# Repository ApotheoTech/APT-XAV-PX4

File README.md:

# APT-XAV-PX4
Copyright 2022 ApotheoTech LLC

# Description

APT-XAV-PX4 is a PX4 based flight controller following FMUv5X. It has a SODIMM connector that is compatible with Nvidia's Jetson Nano, Xavier NX, and TX2 boards. It is a derivative of AntMicros' Jetson Nano Baseboard. I converted the board to Kicad using an Altium to Kicad converter available in the nightly builds of Kicad 6.0.

The APT-XAV-PX4 breaks out Ethernet, USB-C, HDMI, DisplayPort, 2 Raspberry PiCam MIPI connectors (2lane and 4 lane) and a connector for Alvium Sensors. The pinout for the Alvium connector must be used in conjunction with AntMicro's flex cables.

https://user-images.githubusercontent.com/43386283/153778050-1cda64f4-45f2-4941-b6fc-7a415ffa1639.mp4

# Where to Buy

The prototypes for this board were not built due to a combination of a lack of funds, and a redirection of focus to another project February of 2021. If you are interested in supporting the project, or wish to create the prototypes, I have most of the BOM in stock. 

For inquires email me at chance189[at]knights.ucf.edu

# Referenced Works
* [AntMicro Jetson Nano BaseBoard](https://github.com/antmicro/jetson-nano-baseboard)
* [PX4 Hardware](https://github.com/pixhawk/Hardware)

# Licensing

I was unsure how to license it based on AntMicro's Apache License. Due to recreating the work from Altium to Kicad, I was unable to preserve the "unmodified" files from the modified files. All modified files are released under the GPLV3 License.

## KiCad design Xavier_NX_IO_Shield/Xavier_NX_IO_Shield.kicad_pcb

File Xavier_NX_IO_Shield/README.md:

# APT-XAV-PX4 IO SHIELD
Copyright 2022 ApotheoTech LLC

# Description

The IO shield breaks out all the signals to usable interfacing connectors as specified in DS-010 (Pixhawk Autopilot Bus Standard) Revision 0.4.0. 
Interface includes 8 PWM FMU channels, 8 IO PWM channels, SBUS, GPS, UART, SPI, and CANBUS. 

# Where to Buy

The prototypes for this board were not built due to a combination of a lack of funds, and a redirection of focus to another project February of 2021. If you are interested in supporting the project, or wish to create the prototypes, I have most of the BOM in stock. 

For inquires email me at chance189[at]knights.ucf.edu

# Referenced Works
* [PX4 Hardware](https://github.com/pixhawk/Hardware)

# Licensing

Released under the GPLV3 License.

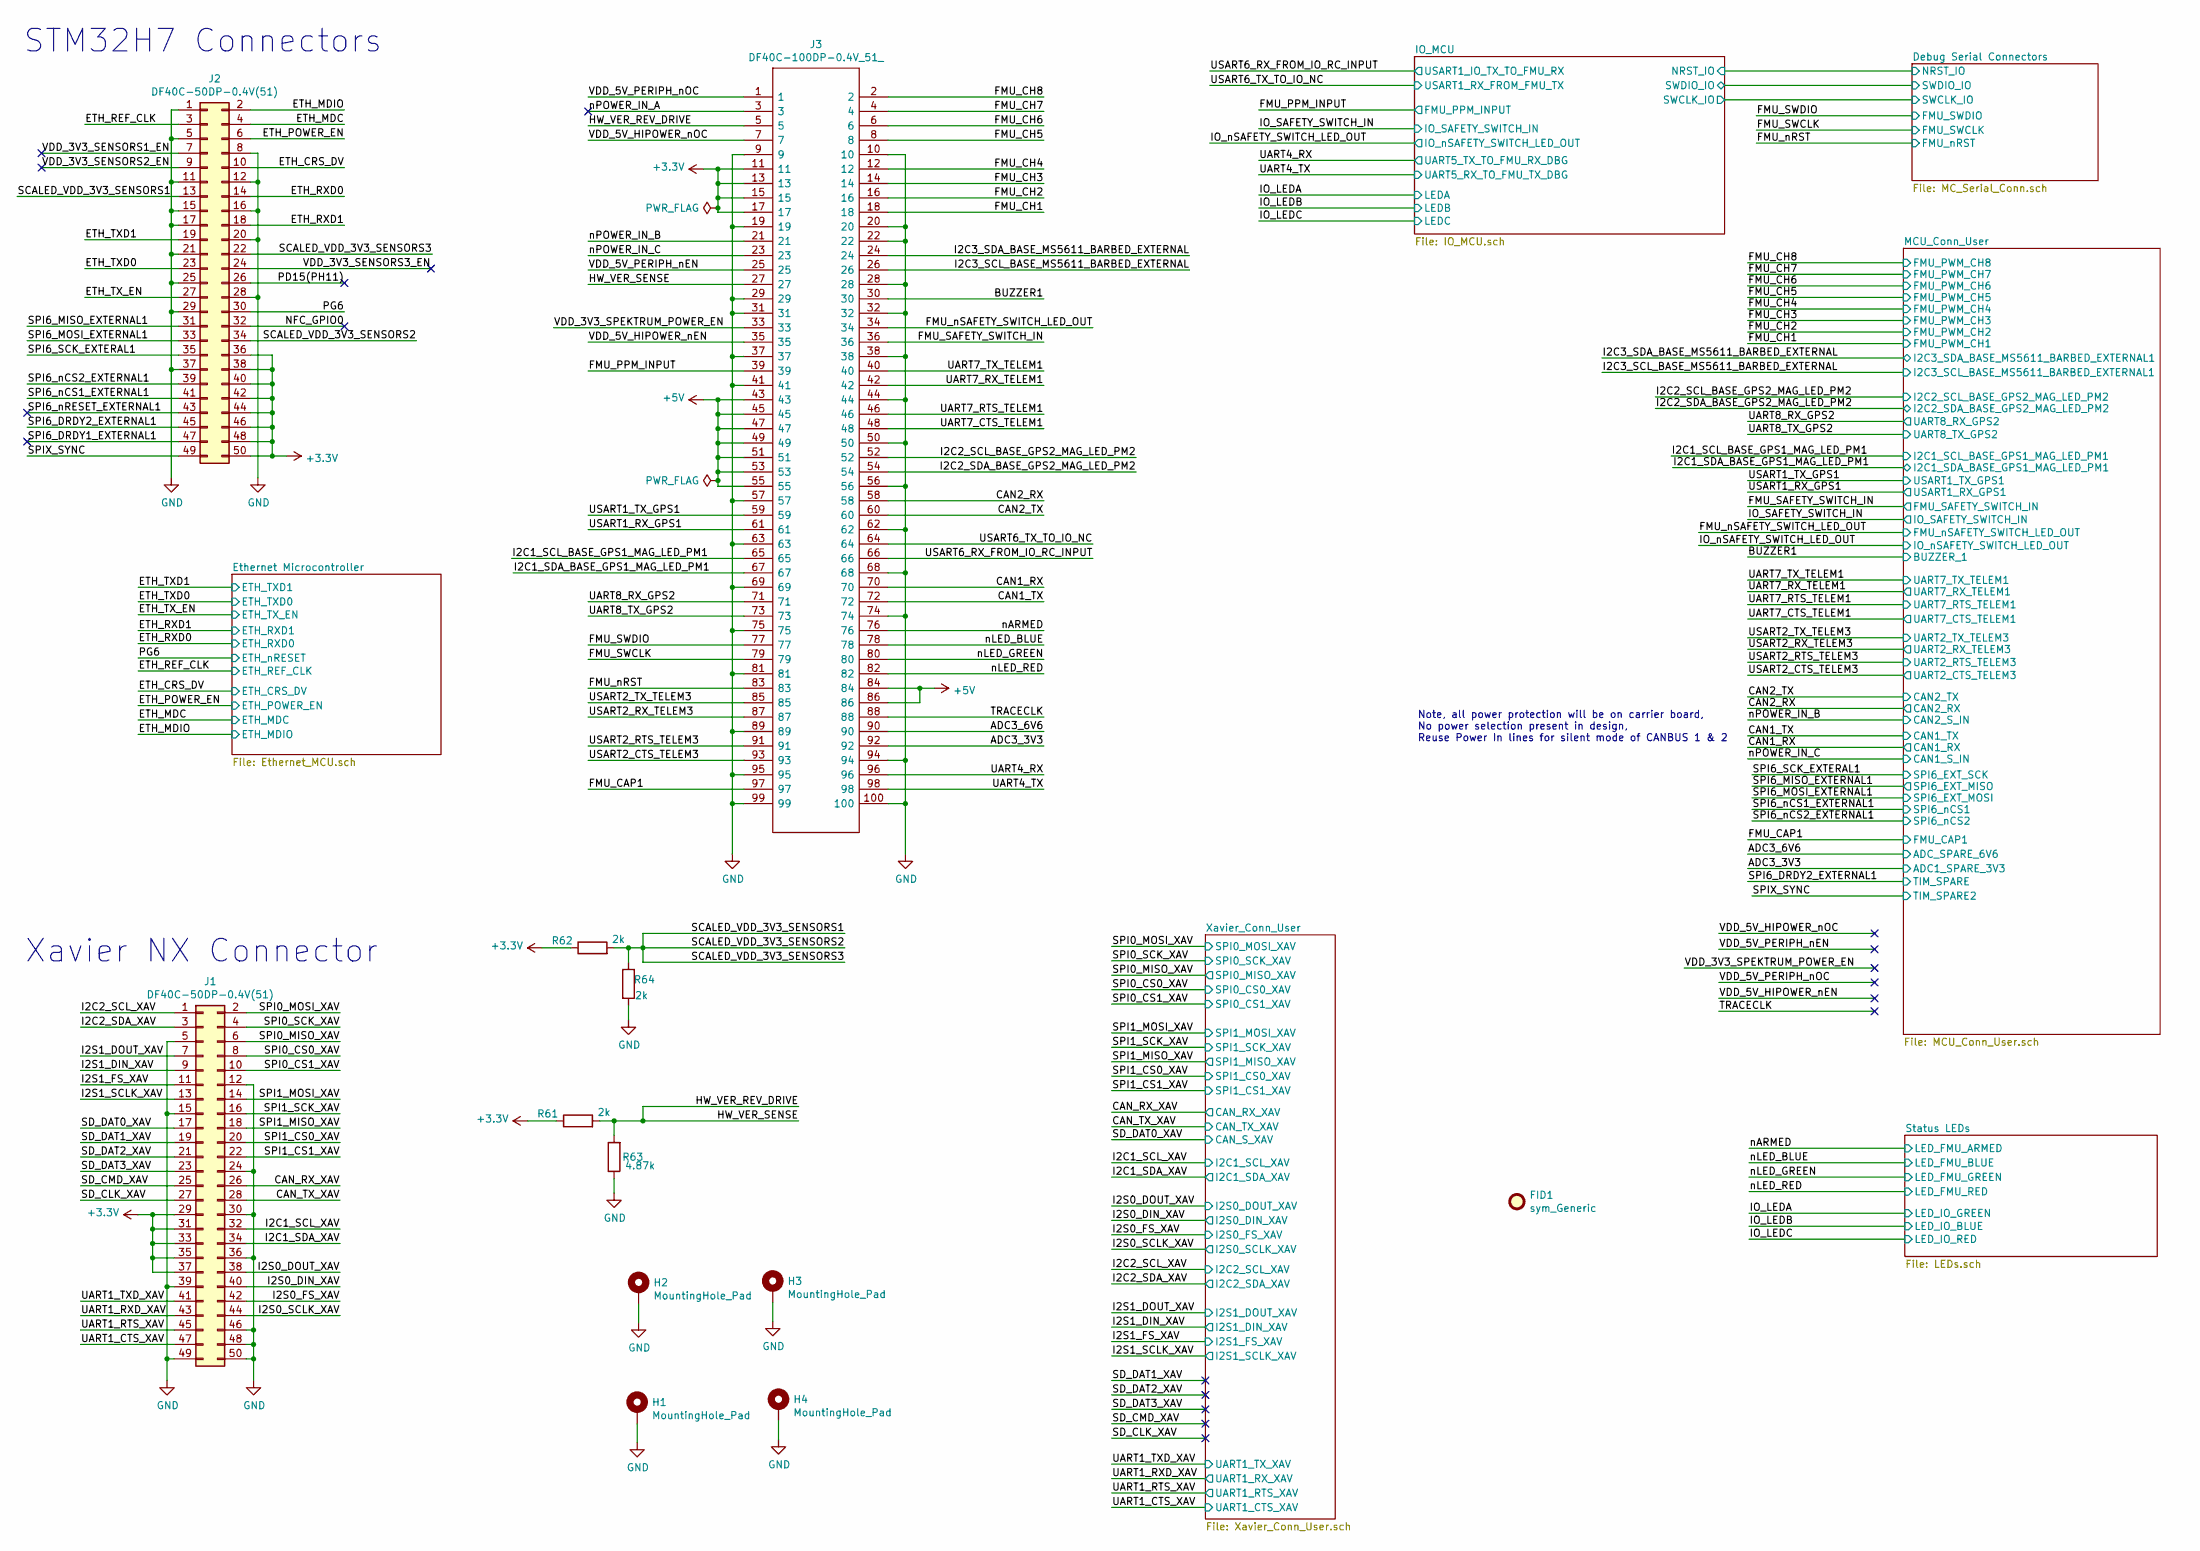
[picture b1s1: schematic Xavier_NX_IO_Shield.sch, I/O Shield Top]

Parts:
FID1: sym_Generic; ApotheoTech_Sym
H1: MountingHole_Pad; 9774015151R
H2, H3, H4: MountingHole_Pad; MountingHole_2.5mm_Pad
J1, J2: DF40C-50DP-0.4V(51); DF40C50DP04V51
J3: DF40C-100DP-0.4V_51_; DF40C100DP04V51; Mouser Part Number 798-DF40C100DP0.4V51
R61, R62, R64: 2k; R_0402_1005Metric; PartNumber CRCW04022K00FKED
R63: 4.87k; R_0402_1005Metric; PartNumber ERJ-2RKF4871X

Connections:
+3V3: J1.29, J1.31, J1.33, J1.35, J1.37, J2.36, J2.38, J2.40, J2.42, J2.44, J2.46, J2.48, J2.50, J3.11, J3.13, J3.15, J3.17, R61.1, R62.1; also elsewhere on the board
+5V: J3.43, J3.45, J3.47, J3.49, J3.51, J3.53, J3.55, J3.84, J3.86; also elsewhere on the board
/ADC3_3V3: J3.92; also elsewhere on the board
/ADC3_6V6: J3.90; also elsewhere on the board
/BUZZER1: J3.30; also elsewhere on the board
/CAN1_RX: J3.70; also elsewhere on the board
/CAN1_TX: J3.72; also elsewhere on the board
/CAN2_RX: J3.58; also elsewhere on the board
/CAN2_TX: J3.60; also elsewhere on the board
/CAN_RX_XAV: J1.26; also elsewhere on the board
/CAN_TX_XAV: J1.28; also elsewhere on the board
/ETH_CRS_DV: J2.10; also elsewhere on the board
/ETH_MDC: J2.4; also elsewhere on the board
/ETH_MDIO: J2.2; also elsewhere on the board
/ETH_POWER_EN: J2.6; also elsewhere on the board
/ETH_REF_CLK: J2.3; also elsewhere on the board
/ETH_RXD0: J2.14; also elsewhere on the board
/ETH_RXD1: J2.18; also elsewhere on the board
/ETH_TXD0: J2.23; also elsewhere on the board
/ETH_TXD1: J2.19; also elsewhere on the board
/ETH_TX_EN: J2.27; also elsewhere on the board
/FMU_CAP1: J3.97; also elsewhere on the board
/FMU_CH1: J3.18; also elsewhere on the board
/FMU_CH2: J3.16; also elsewhere on the board
/FMU_CH3: J3.14; also elsewhere on the board
/FMU_CH4: J3.12; also elsewhere on the board
/FMU_CH5: J3.8; also elsewhere on the board
/FMU_CH6: J3.6; also elsewhere on the board
/FMU_CH7: J3.4; also elsewhere on the board
/FMU_CH8: J3.2; also elsewhere on the board
/FMU_PPM_INPUT: J3.39; also elsewhere on the board
/FMU_SAFETY_SWITCH_IN: J3.36; also elsewhere on the board
/FMU_SWCLK: J3.79; also elsewhere on the board
/FMU_SWDIO: J3.77; also elsewhere on the board
/FMU_nRST: J3.83; also elsewhere on the board
/FMU_nSAFETY_SWITCH_LED_OUT: J3.34; also elsewhere on the board
/HW_VER_REV_DRIVE: J3.5, J3.27, R61.2, R63.2
/I2C1_SCL_BASE_GPS1_MAG_LED_PM1: J3.65; also elsewhere on the board
/I2C1_SCL_XAV: J1.32; also elsewhere on the board
/I2C1_SDA_BASE_GPS1_MAG_LED_PM1: J3.67; also elsewhere on the board
/I2C1_SDA_XAV: J1.34; also elsewhere on the board
/I2C2_SCL_BASE_GPS2_MAG_LED_PM2: J3.52; also elsewhere on the board
/I2C2_SCL_XAV: J1.1; also elsewhere on the board
/I2C2_SDA_BASE_GPS2_MAG_LED_PM2: J3.54; also elsewhere on the board
/I2C2_SDA_XAV: J1.3; also elsewhere on the board
/I2C3_SCL_BASE_MS5611_BARBED_EXTERNAL: J3.26; also elsewhere on the board
/I2C3_SDA_BASE_MS5611_BARBED_EXTERNAL: J3.24; also elsewhere on the board
/I2S0_DIN_XAV: J1.40; also elsewhere on the board
/I2S0_DOUT_XAV: J1.38; also elsewhere on the board
/I2S0_FS_XAV: J1.42; also elsewhere on the board
/I2S0_SCLK_XAV: J1.44; also elsewhere on the board
/I2S1_DIN_XAV: J1.9; also elsewhere on the board
/I2S1_DOUT_XAV: J1.7; also elsewhere on the board
/I2S1_FS_XAV: J1.11; also elsewhere on the board
/I2S1_SCLK_XAV: J1.13; also elsewhere on the board
/NFC_GPIO0: J2.32
/PD15(PH11): J2.26
/PG6: J2.30; also elsewhere on the board
/SCALED_VDD_3V3_SENSORS1: J2.13, J2.22, J2.34, R62.2, R64.1
/SD_CLK_XAV: J1.27
/SD_CMD_XAV: J1.25
/SD_DAT0_XAV: J1.17; also elsewhere on the board
/SD_DAT1_XAV: J1.19
/SD_DAT2_XAV: J1.21
/SD_DAT3_XAV: J1.23
/SPI0_CS0_XAV: J1.8; also elsewhere on the board
/SPI0_CS1_XAV: J1.10; also elsewhere on the board
/SPI0_MISO_XAV: J1.6; also elsewhere on the board
/SPI0_MOSI_XAV: J1.2; also elsewhere on the board
/SPI0_SCK_XAV: J1.4; also elsewhere on the board
/SPI1_CS0_XAV: J1.20; also elsewhere on the board
/SPI1_CS1_XAV: J1.22; also elsewhere on the board
/SPI1_MISO_XAV: J1.18; also elsewhere on the board
/SPI1_MOSI_XAV: J1.14; also elsewhere on the board
/SPI1_SCK_XAV: J1.16; also elsewhere on the board
/SPI6_DRDY1_EXTERNAL1: J2.47
/SPI6_DRDY2_EXTERNAL1: J2.45; also elsewhere on the board
/SPI6_MISO_EXTERNAL1: J2.31; also elsewhere on the board
/SPI6_MOSI_EXTERNAL1: J2.33; also elsewhere on the board
/SPI6_SCK_EXTERAL1: J2.35; also elsewhere on the board
/SPI6_nCS1_EXTERNAL1: J2.41; also elsewhere on the board
/SPI6_nCS2_EXTERNAL1: J2.39; also elsewhere on the board
/SPI6_nRESET_EXTERNAL1: J2.43
/SPIX_SYNC: J2.49; also elsewhere on the board
/TRACECLK: J3.88
/UART1_CTS_XAV: J1.47; also elsewhere on the board
/UART1_RTS_XAV: J1.45; also elsewhere on the board
/UART1_RXD_XAV: J1.43; also elsewhere on the board
/UART1_TXD_XAV: J1.41; also elsewhere on the board
/UART4_RX: J3.96; also elsewhere on the board
/UART4_TX: J3.98; also elsewhere on the board
/UART7_CTS_TELEM1: J3.48; also elsewhere on the board
/UART7_RTS_TELEM1: J3.46; also elsewhere on the board
/UART7_RX_TELEM1: J3.42; also elsewhere on the board
/UART7_TX_TELEM1: J3.40; also elsewhere on the board
/UART8_RX_GPS2: J3.71; also elsewhere on the board
/UART8_TX_GPS2: J3.73; also elsewhere on the board
/USART1_RX_GPS1: J3.61; also elsewhere on the board
/USART1_TX_GPS1: J3.59; also elsewhere on the board
/USART2_CTS_TELEM3: J3.93; also elsewhere on the board
/USART2_RTS_TELEM3: J3.91; also elsewhere on the board
/USART2_RX_TELEM3: J3.87; also elsewhere on the board
/USART2_TX_TELEM3: J3.85; also elsewhere on the board
/USART6_RX_FROM_IO_RC_INPUT: J3.66; also elsewhere on the board
/USART6_TX_TO_IO_NC: J3.64; also elsewhere on the board
/VDD_3V3_SENSORS1_EN: J2.7
/VDD_3V3_SENSORS2_EN: J2.9
/VDD_3V3_SENSORS3_EN: J2.24
/VDD_3V3_SPEKTRUM_POWER_EN: J3.33
/VDD_5V_HIPOWER_nEN: J3.35
/VDD_5V_HIPOWER_nOC: J3.7
/VDD_5V_PERIPH_nEN: J3.25
/VDD_5V_PERIPH_nOC: J3.1
/nARMED: J3.76; also elsewhere on the board
/nLED_BLUE: J3.78; also elsewhere on the board
/nLED_GREEN: J3.80; also elsewhere on the board
/nLED_RED: J3.82; also elsewhere on the board
/nPOWER_IN_A: J3.3
/nPOWER_IN_B: J3.21; also elsewhere on the board
/nPOWER_IN_C: J3.23; also elsewhere on the board
GND: H1.1, H2.1, H3.1, H4.1, J1.5, J1.12, J1.15, J1.24, J1.30, J1.36, J1.39, J1.46, J1.48, J1.49, J1.50, J2.1, J2.5, J2.8, J2.11, J2.12, J2.15, J2.16, J2.17, J2.20, J2.21, J2.25, J2.28, J2.29, J2.37, J3.9, J3.10, J3.19, J3.20, J3.22, J3.28, J3.29, J3.31, J3.32, J3.37, J3.38, J3.41, J3.44, J3.50, J3.56, J3.57, J3.62, J3.63, J3.68, J3.69, J3.74, J3.75, J3.81, J3.89, J3.94, J3.95, J3.99, J3.100, R63.1, R64.2; also elsewhere on the board

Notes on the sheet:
STM32H7 Connectors
Xavier NX Connector
Note, all power protection will be on carrier board, No power selection present in design, Reuse Power In lines for silent mode of CANBUS 1 & 2

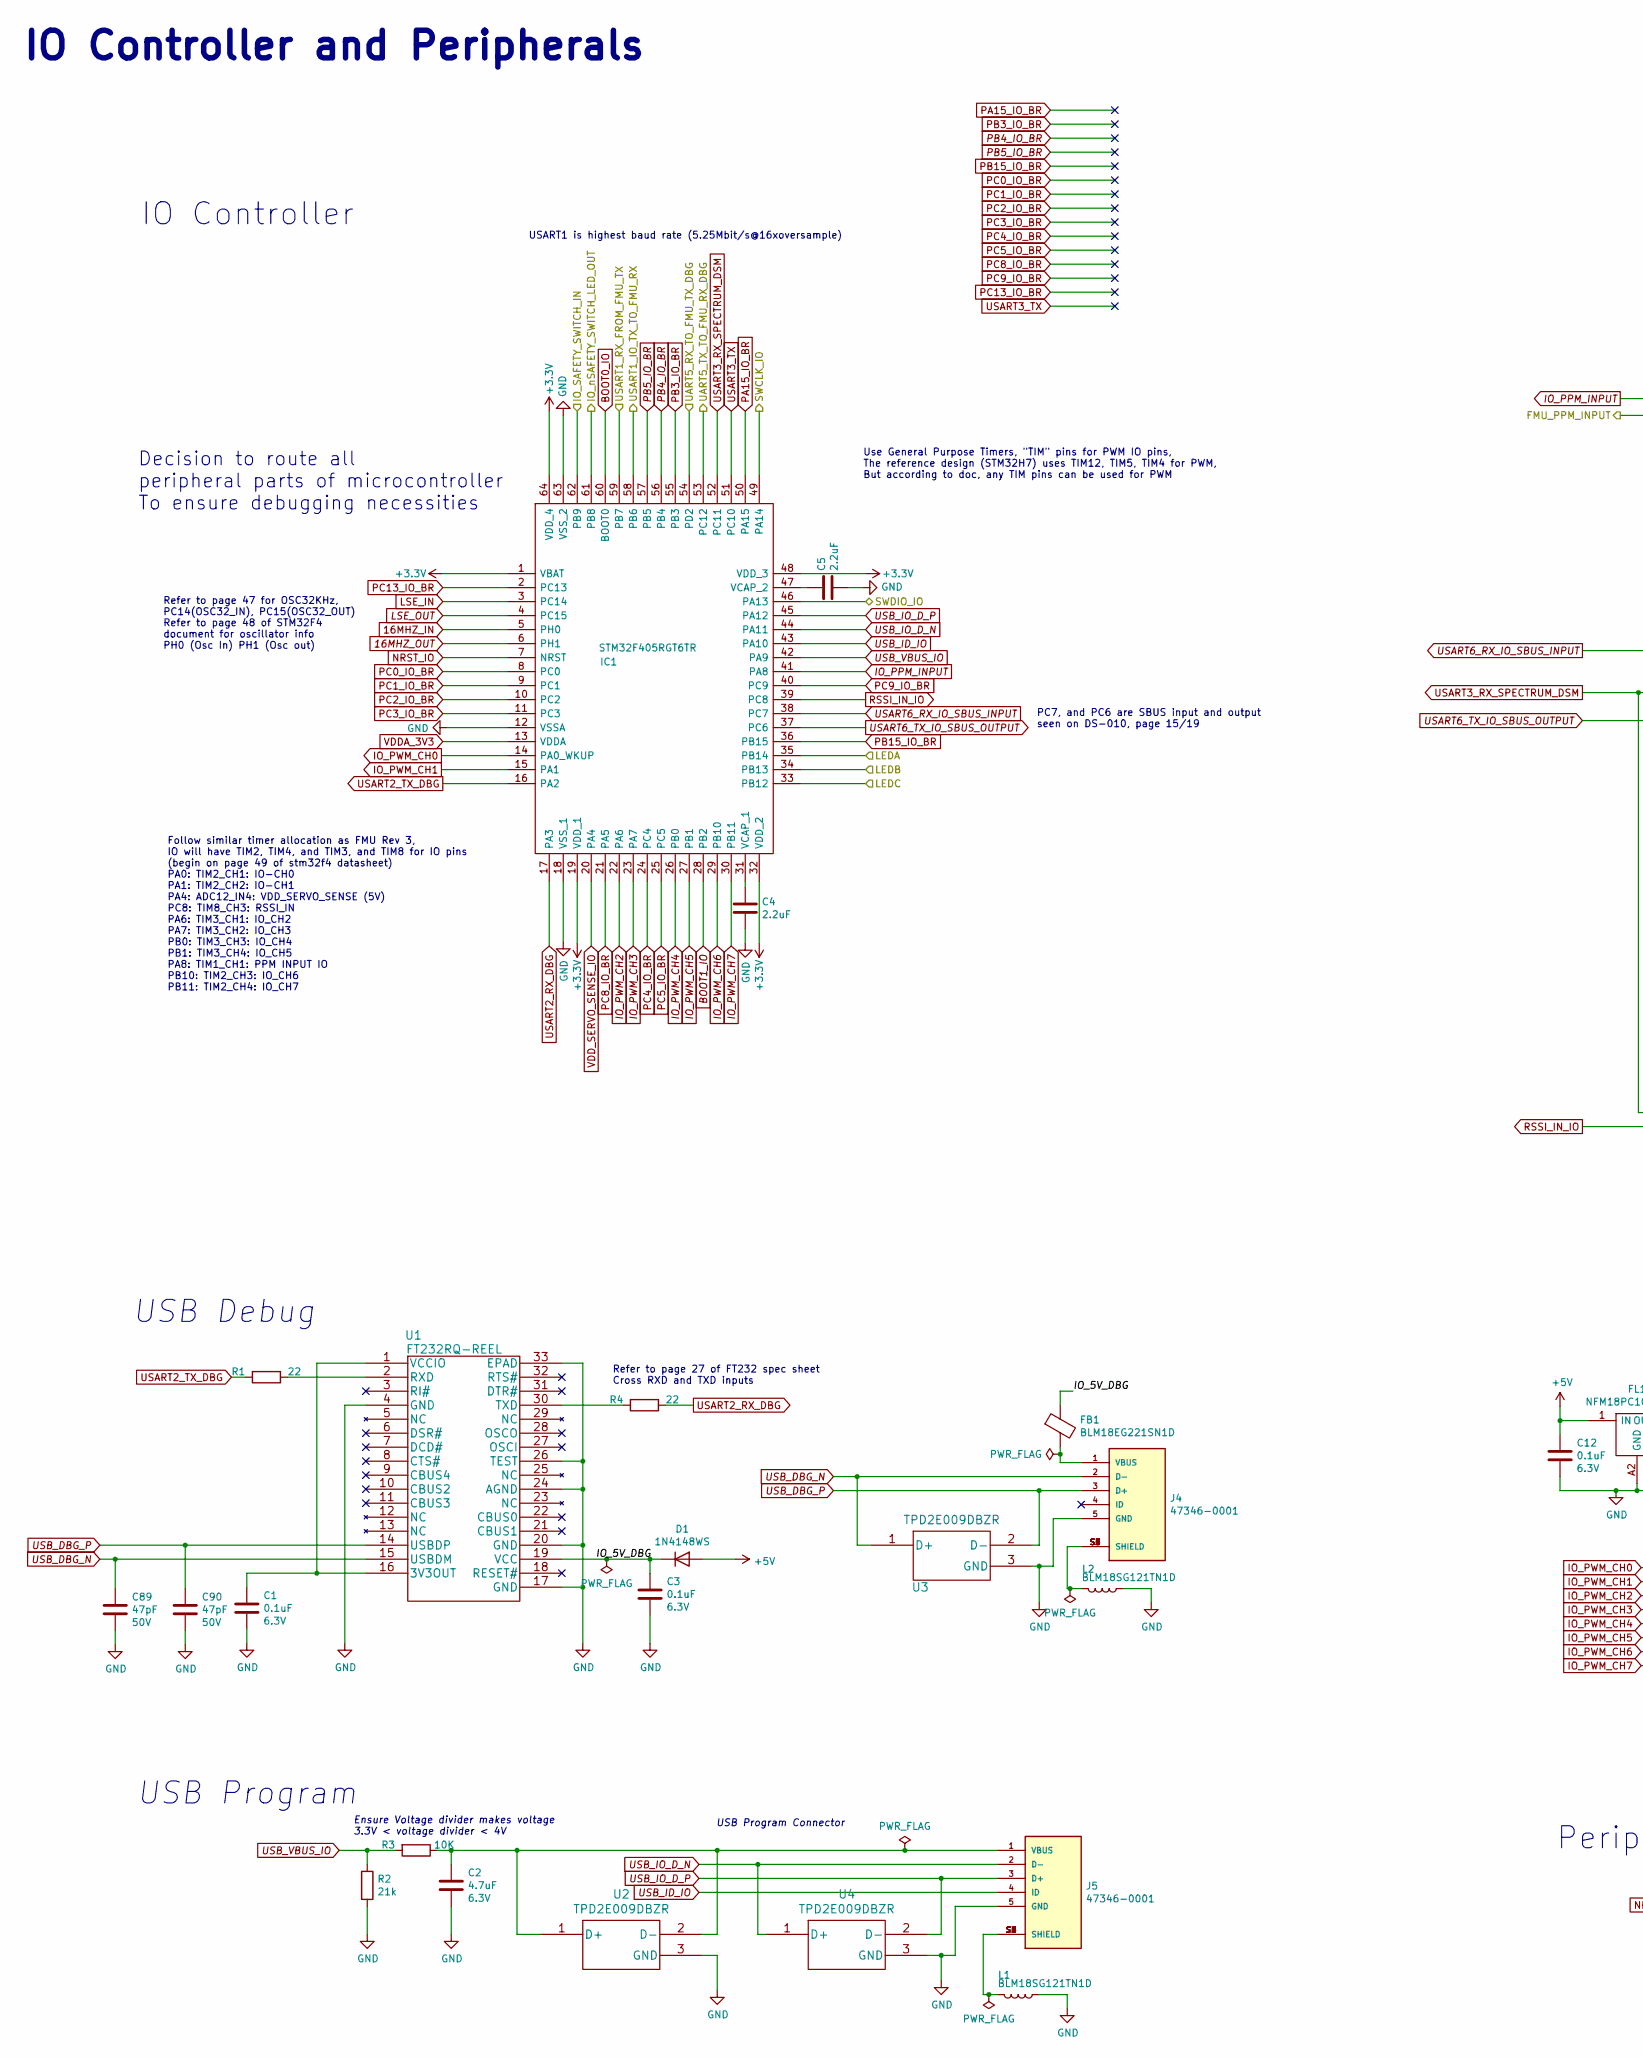
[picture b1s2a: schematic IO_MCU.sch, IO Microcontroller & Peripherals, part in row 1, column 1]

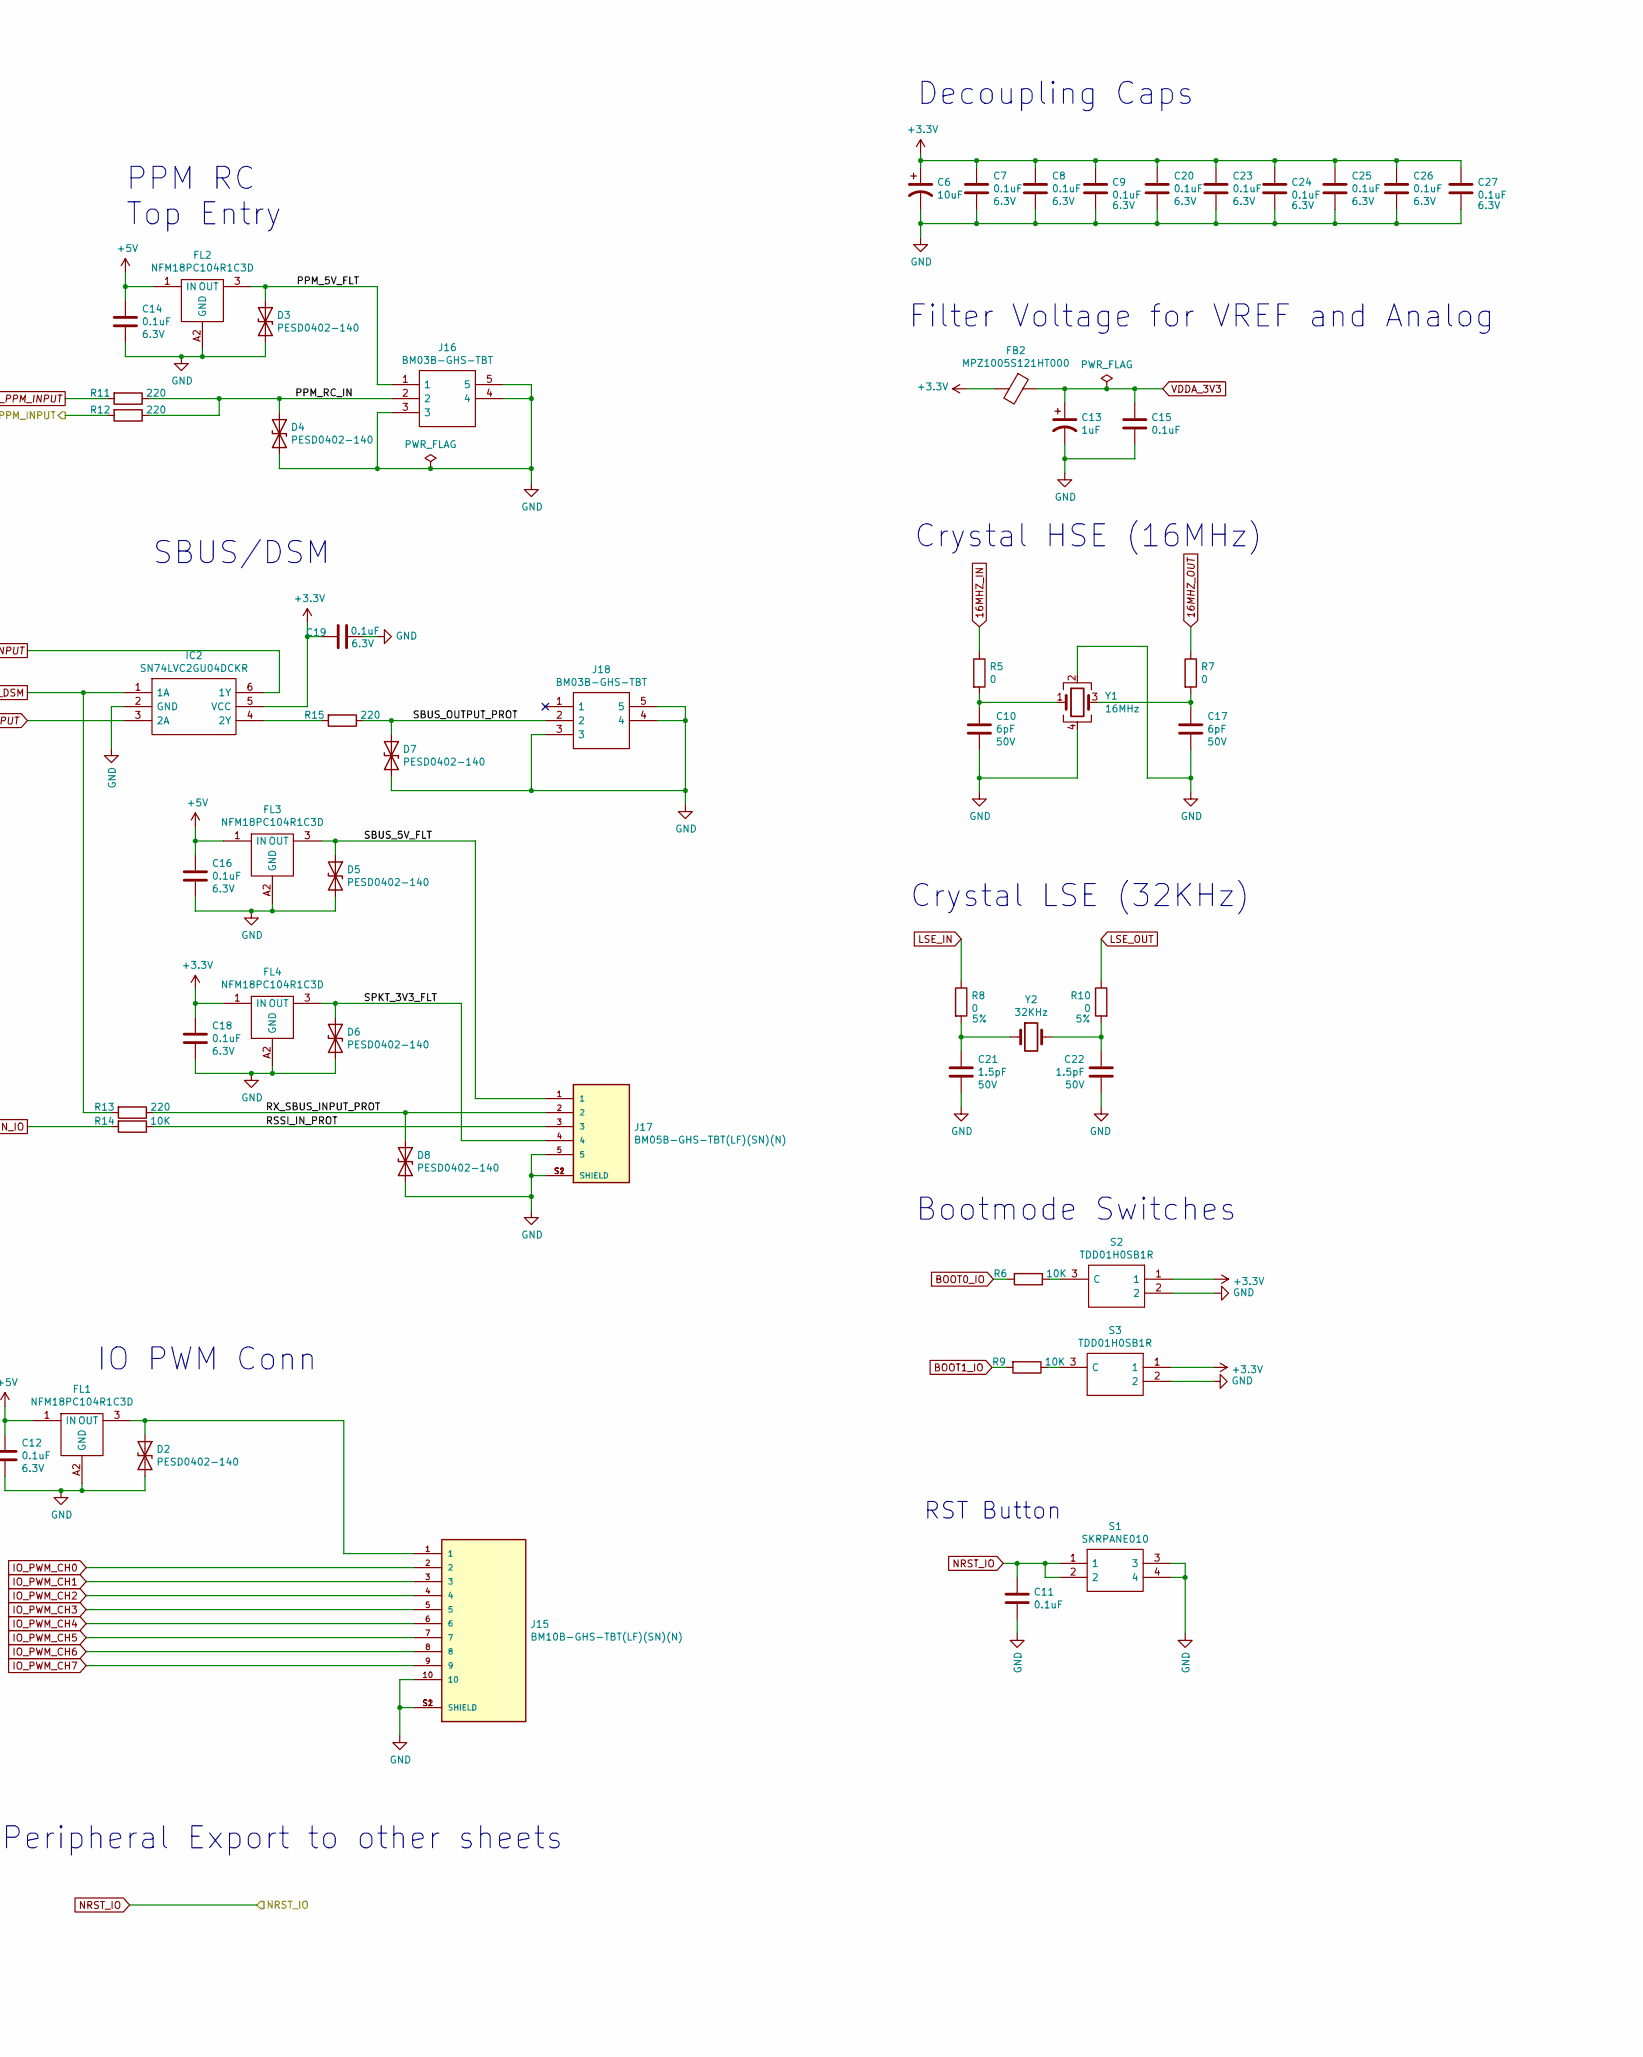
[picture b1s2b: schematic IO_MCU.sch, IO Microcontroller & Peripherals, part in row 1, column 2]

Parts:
C1, C3, C7, C8, C9, C11, C12, C14, C15, C16, C18, C19, C20, C23, C24, C25, C26, C27: 0.1uF; C_0402_1005Metric; Voltage 6.3V; PartNumber C1005X5R0J104K050BA
C2: 4.7uF; C_0402_1005Metric; Voltage 6.3V; PartNumber GRM155R60J475ME87D
C4, C5: 2.2uF; C_0603_1608Metric; Voltage 50V; PartNumber CC0603KRX5R9BB225
C6: 10uF; CP_EIA-1608-10_AVX-L; Voltage 10V; PartNumber F381A106MMAAH1
C10, C17: 6pF; C_0402_1005Metric; Voltage 50V; PartNumber CC0402BRNPO9BN6R0
C13: 1uF; CP_EIA-1608-10_AVX-L; Voltage 10V; PartNumber TACL105K010RTA
C21, C22: 1.5pF; C_0603_1608Metric; Voltage 50V; PartNumber CC0603BRNPO9BN1R5
C89, C90: 47pF; C_0402_1005Metric; Voltage 50V; PartNumber C0402C470J5GACTU
D1: 1N4148WS; D_SOD-323F
D2, D3, D4, D5, D6, D7, D8: PESD0402-140; PESD0402
FB1: BLM18EG221SN1D; C_0603_1608Metric
FB2: MPZ1005S121HT000; C_0402_1005Metric
FL1, FL2, FL3, FL4: NFM18PC104R1C3D; Manufacturer_Part_Number NFM18PC104R1C3D
IC1: STM32F405RGT6TR; Mouser Part Number 511-STM32F405RGT6TR
IC2: SN74LVC2GU04DCKR; Mouser Part Number 595-SN74LVC2GU04DCKR
J4, J5: 47346-0001; MOLEX_47346-0001; PARTREV E
J15: BM10B-GHS-TBT(LF)(SN)(N); PARTREV N/A
J16, J18: BM03B-GHS-TBT; Manufacturer_Part_Number SM03B-GHS-TB(LF)(SN)
J17: BM05B-GHS-TBT(LF)(SN)(N); BM05B-GHS-TBT; PARTREV N/A
L1, L2: BLM18SG121TN1D; L_0603_1608Metric
R1, R4: 22; R_0402_1005Metric; PartNumber CRCW040222R0FKEDC
R2: 21k; R_0402_1005Metric; PartNumber CRCW040221K0FKED
R3, R6, R9, R14: 10K; R_0402_1005Metric; PartNumber ERJ-2RKF1002X
R5, R7, R8, R10: 0; R_0402_1005Metric; PartNumber RC0402JR-070RL
R11, R12, R13, R15: 220; R_0402_1005Metric; PartNumber RC0402JR-07220RL
S1: SKRPANE010; SKRPADE010; Mouser Part Number 688-SKRPANE010
S2, S3: TDD01H0SB1R; Mouser Part Number 611-TDD01H0SB1R
U1: FT232RQ-REEL
U2, U3, U4: TPD2E009DBZR
Y1: 16MHz; NX3225GA16000MSTDCRG1; PartNumber NX3225GA-16.000M-STD-CRG-1
Y2: 32KHz; NX3215SA32768KEXS00AMU00003; PartNumber NX3215SA-32.768KHZ-EXS00A-MU00525

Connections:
16MHZ_IN: IC1.5 (PH0), R5.1
16MHZ_OUT: IC1.6 (PH1), R7.1
+3V3: C6.1, C7.1, C8.1, C9.1, C18.1, C19.1, C20.1, C23.1, C24.1, C25.1, C26.1, C27.1, FB2.2, FL4.1 (IN), IC1.1 (VBAT), IC1.19 (VDD_1), IC1.32 (VDD_2), IC1.48 (VDD_3), IC1.64 (VDD_4), IC2.5 (VCC), S2.1, S3.1; also elsewhere on the board
+5V: C12.1, C14.1, C16.1, D1.2 (A), FL1.1 (IN), FL2.1 (IN), FL3.1 (IN); also elsewhere on the board
/Debug Serial Connectors/SWCLK_IO: IC1.49 (PA14); also elsewhere on the board
/Debug Serial Connectors/SWDIO_IO: IC1.46 (PA13); also elsewhere on the board
/FMU_PPM_INPUT: R12.2; also elsewhere on the board
/IO_LEDA: IC1.35 (PB14); also elsewhere on the board
/IO_LEDB: IC1.34 (PB13); also elsewhere on the board
/IO_LEDC: IC1.33 (PB12); also elsewhere on the board
/IO_MCU/IO_5V_DBG: C3.1, D1.1 (K), FB1.1, U1.19 (VCC)
/IO_MCU/PPM_5V_FLT: D3.1 (A1), FL2.3 (OUT), J16.1
/IO_MCU/PPM_RC_IN: D4.1 (A1), J16.2, R11.1, R12.1
/IO_MCU/RSSI_IN_PROT: J17.3, R14.1
/IO_MCU/RX_SBUS_INPUT_PROT: D8.1 (A1), J17.2, R13.1
/IO_MCU/SBUS_5V_FLT: D5.1 (A1), FL3.3 (OUT), J17.1
/IO_MCU/SBUS_OUTPUT_PROT: D7.1 (A1), J18.2, R15.1
/IO_MCU/SPKT_3V3_FLT: D6.1 (A1), FL4.3 (OUT), J17.4
/IO_SAFETY_SWITCH_IN: IC1.62 (PB9); also elsewhere on the board
/IO_nSAFETY_SWITCH_LED_OUT: IC1.61 (PB8); also elsewhere on the board
/UART4_RX: IC1.53 (PC12); also elsewhere on the board
/UART4_TX: IC1.54 (PD2); also elsewhere on the board
/USART6_RX_FROM_IO_RC_INPUT: IC1.58 (PB6); also elsewhere on the board
/USART6_TX_TO_IO_NC: IC1.59 (PB7); also elsewhere on the board
BOOT0_IO: IC1.60 (BOOT0), R6.2
BOOT1_IO: IC1.28 (PB2), R9.2
GND: C1.2, C2.2, C3.2, C4.2, C5.2, C6.2, C7.2, C8.2, C9.2, C10.2, C11.2, C12.2, C13.2, C14.2, C15.2, C16.2, C17.2, C18.2, C19.2, C20.2, C21.2, C22.2, C23.2, C24.2, C25.2, C26.2, C27.2, C89.2, C90.2, D2.2 (A2), D3.2 (A2), D4.2 (A2), D5.2 (A2), D6.2 (A2), D7.2 (A2), D8.2 (A2), FL1.A2 (GND), FL2.A2 (GND), FL3.A2 (GND), FL4.A2 (GND), IC1.12 (VSSA), IC1.18 (VSS_1), IC1.63 (VSS_2), IC2.2 (GND), J4.5 (GND), J5.5 (GND), J15.10, J15.S1 (SHIELD), J15.S2 (SHIELD), J16.3, J16.4, J16.5, J17.5, J17.S1 (SHIELD), J17.S2 (SHIELD), J18.3, J18.4, J18.5, L1.1, L2.1, R2.2, S1.3, S1.4, S2.2, S3.2, U1.4 (GND), U1.17 (GND), U1.20 (GND), U1.24 (AGND), U1.26 (TEST), U1.33 (EPAD), U2.3 (GND), U3.3 (GND), U4.3 (GND), Y1.2, Y1.4; also elsewhere on the board
IO_PPM_INPUT: IC1.41 (PA8), R11.2
IO_PWM_CH0: IC1.14 (PA0_WKUP), J15.2
IO_PWM_CH1: IC1.15 (PA1), J15.3
IO_PWM_CH2: IC1.22 (PA6), J15.4
IO_PWM_CH3: IC1.23 (PA7), J15.5
IO_PWM_CH4: IC1.26 (PB0), J15.6
IO_PWM_CH5: IC1.27 (PB1), J15.7
IO_PWM_CH6: IC1.29 (PB10), J15.8
IO_PWM_CH7: IC1.30 (PB11), J15.9
LSE_IN: IC1.3 (PC14), R8.1
LSE_OUT: IC1.4 (PC15), R10.1
NRST_IO: C11.1, IC1.7 (NRST), S1.1, S1.2; also elsewhere on the board
unnamed: C1.1, U1.1 (VCCIO), U1.16 (3V3OUT)
unnamed: C2.1, J5.1 (VBUS), R3.1, U2.1 (D+), U2.2 (D-)
unnamed: C4.1, IC1.31 (VCAP_1)
unnamed: C5.1, IC1.47 (VCAP_2)
unnamed: C10.1, R5.2, Y1.1
unnamed: C17.1, R7.2, Y1.3
unnamed: C21.1, R8.2, Y2.1
unnamed: C22.1, R10.2, Y2.2
unnamed: D2.1 (A1), FL1.3 (OUT), J15.1
unnamed: FB1.2, J4.1 (VBUS)
unnamed: IC2.4 (2Y), R15.2
unnamed: J4.S1 (SHIELD), J4.S2 (SHIELD), J4.S3 (SHIELD), J4.S4 (SHIELD), J4.S5 (SHIELD), J4.S6 (SHIELD), L2.2
unnamed: J5.S1 (SHIELD), J5.S2 (SHIELD), J5.S3 (SHIELD), J5.S4 (SHIELD), J5.S5 (SHIELD), J5.S6 (SHIELD), L1.2
unnamed: R1.1, U1.2 (RXD)
unnamed: R4.2, U1.30 (TXD)
unnamed: R6.1, S2.3 (C)
unnamed: R9.1, S3.3 (C)
PA15_IO_BR: IC1.50 (PA15)
PB3_IO_BR: IC1.55 (PB3)
PB4_IO_BR: IC1.56 (PB4)
PB5_IO_BR: IC1.57 (PB5)
PB15_IO_BR: IC1.36 (PB15)
PC0_IO_BR: IC1.8 (PC0)
PC1_IO_BR: IC1.9 (PC1)
PC2_IO_BR: IC1.10 (PC2)
PC3_IO_BR: IC1.11 (PC3)
PC4_IO_BR: IC1.24 (PC4)
PC5_IO_BR: IC1.25 (PC5)
PC8_IO_BR: IC1.21 (PA5)
PC9_IO_BR: IC1.40 (PC9)
PC13_IO_BR: IC1.2 (PC13)
RSSI_IN_IO: IC1.39 (PC8), R14.2
USART2_RX_DBG: IC1.17 (PA3), R4.1
USART2_TX_DBG: IC1.16 (PA2), R1.2
USART3_RX_SPECTRUM_DSM: IC1.52 (PC11), IC2.1 (1A), R13.2
USART3_TX: IC1.51 (PC10)
USART6_RX_IO_SBUS_INPUT: IC1.38 (PC7), IC2.6 (1Y)
USART6_TX_IO_SBUS_OUTPUT: IC1.37 (PC6), IC2.3 (2A)
USB_DBG_N: C89.1, J4.2 (D-), U1.15 (USBDM), U3.1 (D+)
USB_DBG_P: C90.1, J4.3 (D+), U1.14 (USBDP), U3.2 (D-)
USB_ID_IO: IC1.43 (PA10), J5.4 (ID)
USB_IO_D_N: IC1.44 (PA11), J5.2 (D-), U4.1 (D+)
USB_IO_D_P: IC1.45 (PA12), J5.3 (D+), U4.2 (D-)
USB_VBUS_IO: IC1.42 (PA9), R2.1, R3.2
VDDA_3V3: C13.1, C15.1, FB2.1, IC1.13 (VDDA)
VDD_SERVO_SENSE_IO: IC1.20 (PA4); also elsewhere on the board

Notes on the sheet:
Use General Purpose Timers, "TIM" pins for PWM IO pins, The reference design (STM32H7) uses TIM12, TIM5, TIM4 for PWM, But according to doc, any TIM pins can be used for PWM
Decoupling Caps
Filter Voltage for VREF and Analog
Crystal HSE (16MHz)
RST Button
Bootmode Switches
USB Program Connector
Ensure Voltage divider makes voltage 3.3V < voltage divider < 4V
USB Program
USB Debug
Refer to page 48 of STM32F4 document for oscillator info PH0 (Osc In) PH1 (Osc out)
USART1 is highest baud rate (5.25Mbit/s@16xoversample)
PC7, and PC6 are SBUS input and output seen on DS-010, page 15/19
Decision to route all peripheral parts of microcontroller To ensure debugging necessities
Refer to page 47 for OSC32KHz, PC14(OSC32_IN), PC15(OSC32_OUT)
Crystal LSE (32KHz)
Follow similar timer allocation as FMU Rev 3, IO will have TIM2, TIM4, and TIM3, and TIM8 for IO pins (begin on page 49 of stm32f4 datasheet) PA0: TIM2_CH1: IO-CH0 PA1: TIM2_CH2: IO-CH1 PA4: ADC12_IN4: VDD_SERVO_SENSE (5V) PC8: TIM8_CH3: RSSI_IN PA6: TIM3_CH1: IO_CH2 PA7: TIM3_CH2: IO_CH3 PB0: TIM3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
SBUS/DSM
IO Controller
IO PWM Conn
IO Controller and Peripherals
PPM RC Top Entry
Peripheral Export to other sheets
Refer to page 27 of FT232 spec sheet Cross RXD and TXD inputs
